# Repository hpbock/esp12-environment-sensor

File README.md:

# esp12-environment-sensor
Environment sensor that is powered by a 18650 battery using a dht22 to sense temperature and humidity. Connectivity is provided wireless using an esp12 sleeping deeply most of the time.

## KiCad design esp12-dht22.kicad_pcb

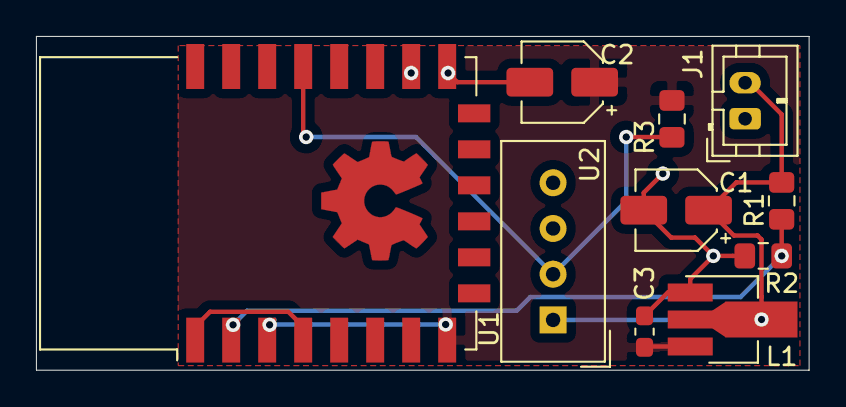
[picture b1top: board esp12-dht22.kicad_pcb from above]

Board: 2 copper layers, 42.9 x 18.5 mm, 11 parts (1 on the bottom side), 7 nets.

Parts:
C1, C2: 10uF; CP_Elec_4x5.8
C3: 100nF; C_0603_1608Metric_Pad1.05x0.95mm_HandSolder
J1: Battery; JST_PH_B2B-PH-K_1x02_P2.00mm_Vertical
L1: HT7333-A; SOT-89-3_Handsoldering
R1: 330k; R_0805_2012Metric_Pad1.15x1.40mm_HandSolder
R2: 100k; R_0805_2012Metric_Pad1.15x1.40mm_HandSolder
R3: 4k7; R_0805_2012Metric_Pad1.15x1.40mm_HandSolder
R4: 2k2; R_0805_2012Metric_Pad1.15x1.40mm_HandSolder
U1: ESP-12E
U2: DHT22; Aosong_DHT11_5.5x12.0_P2.54mm

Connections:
+BATT: C1.1, J1.2, L1.2, R1.1, U2.1
ADC: R1.2, R2.1, U1.2
DHT_Data: R3.2, U1.19, U2.2
DeepSleep: U1.1, U1.4
GND: C1.2, C2.2, C3.2, J1.1, L1.1, R2.2, R4.2, U1.15, U2.4
unnamed: R4.1, U1.16
VCC: C2.1, C3.1, L1.3, R3.1, U1.3, U1.8

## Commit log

2019-07-05 added initial kicad project
2019-07-05 added power supply
2019-07-06 added esp, dht22 and battery voltage divider for adc
2019-07-09 changed data pin from gpio5 to gpio4
2019-07-14 added 100nF caps
2019-07-15 added JST PH connector for battery
2019-07-17 moved via and added date to bottom silkscreen
2019-07-18 removed layer alignment target
2019-07-23 added connection between RST and GPIO16 for wakeup from deep sleep fixes #1
2019-08-19 swapped pins of J1 fixes #4
2019-08-19 connected ENABLE and GPIO15 to boot properly fixes #2
2020-04-02 connected DHT22 to Vbatt fixes #3
2020-06-22 added soldered 18650 battery holder closes #6
2020-06-22 DHT22 is now supplied with Vbat closes #3
